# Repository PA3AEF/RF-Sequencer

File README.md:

# **RF‑Sequencer**

The RF‑Sequencer provides deterministic, safe, and hardware‑independent control of RF transmit and receive path transitions.  
It is designed for radio systems that require strict sequencing, amplifier protection, and predictable relay behavior under all conditions.

The firmware architecture emphasizes clarity, safety, and long‑term maintainability.  
Relay hardware, timing rules, and protection logic are abstracted behind stable interfaces, ensuring consistent operation across diverse station configurations.
Earlier work, such as the concepts published by W1GHZ (Paul Wade) helped establish the fundamental principles of safe RF path control.
This RF‑Sequencer continues that lineage with a modern, firmware‑driven architecture that emphasizes clarity, determinism, and long‑term maintainability.

## **Key Features**

- Deterministic transmit/receive sequencing  
- Integrated protection engine with SAFE‑mode enforcement  
- High‑speed ADC sampling for forward and reflected power  
- VSWR and fast reflected‑spike protection (REF_FAST)
- Hardware‑independent relay abstraction  
- Support for monostable and latching relays  
- Configurable timing and topology  
- Structured event output for external integration  
- Minimal configuration surface  
- Designed for reliability in demanding RF environments  

## **Why Another Sequencer?**

Existing RF sequencers, including the influential **W1GHZ Mark 5**, proved that microcontroller‑based protection can outperform analog timing chains. But modern stations demand more: deterministic firmware behavior, structured telemetry, remote monitoring, fault latching, and safe operation in unattended or tower‑top installations.

This project was created to provide:

- A **fully deterministic** main‑loop architecture  
- **Sub‑millisecond protection paths** (REF_FAST)  
- A **machine‑readable event stream** for dashboards and automation  
- A **human‑readable logging channel** for operators  
- A **calibration system** that adapts to any coupler  
- A **robust SAFE‑mode model** suitable for remote sites  

In short: it’s a **next‑generation MCU sequencer**, built on the ideas that came before but engineered for today’s RF environments.

## **Documentation**

The documentation is organized into several focused areas:

### **Overview**
High‑level conceptual introduction to the system.  
- `docs/overview/overview.md`

### **Architecture**
Detailed subsystem specifications and internal design.  
- `docs/architecture/firmware-architecture.md`  
- `docs/architecture/relay-architecture.md`

### **Integration**
External systems can interact with the sequencer through a structured event stream.  
Events reflect internal state transitions, protection triggers, relay actions, and measurement updates.   
Guidance for consuming sequencer events and coordinating external systems:
- `docs/integration/event-monitoring-example.md`
- `docs/integration/integration-examples.md`
- `docs/integration/integration-guide.md`

### **Quickstart**
Installation‑specific setup and basic configuration.  
- `docs/quickstart/quickstart.md`

### **Reference (optional)**
Command‑line reference, event definitions, and configuration schema.  
- `docs/reference/`

## **Design Philosophy**

The RF‑Sequencer is built around several core principles:

- **Safety first** — protection logic overrides all other behavior  
- **Determinism** — no asynchronous state changes  
- **Hardware abstraction** — relay details are isolated behind stable interfaces  
- **Minimal configuration** — only essential structural parameters are exposed  
- **Predictability** — timing and transitions follow strict rules  

These principles ensure reliable operation in both simple and complex RF installations.

## **Contributing**

Contributions that improve clarity, safety, or maintainability are welcome.  
Please ensure that changes preserve the architectural principles described in the documentation.

# **License**

This project uses a dual‑license model:

- **Firmware:** binary‑only, see `LICENSE_FIRMWARE.md`
- **Hardware:** CERN OHL‑P, see `LICENSE_HARDWARE.md`

A human‑readable summary is provided in:

- `LICENSE_NOTICE.md`

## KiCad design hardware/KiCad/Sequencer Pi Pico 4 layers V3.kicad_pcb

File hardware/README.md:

# Hardware

Everything rekated to Hardware.  PCB's (4 layers!) can be easily ordered from JLCPCB. Submit the production ZIP file located in the PCB section. Files are provided for PCBA (PCB Assembly) but it is expensive for small series. Some experience with SMDsoldering is required.

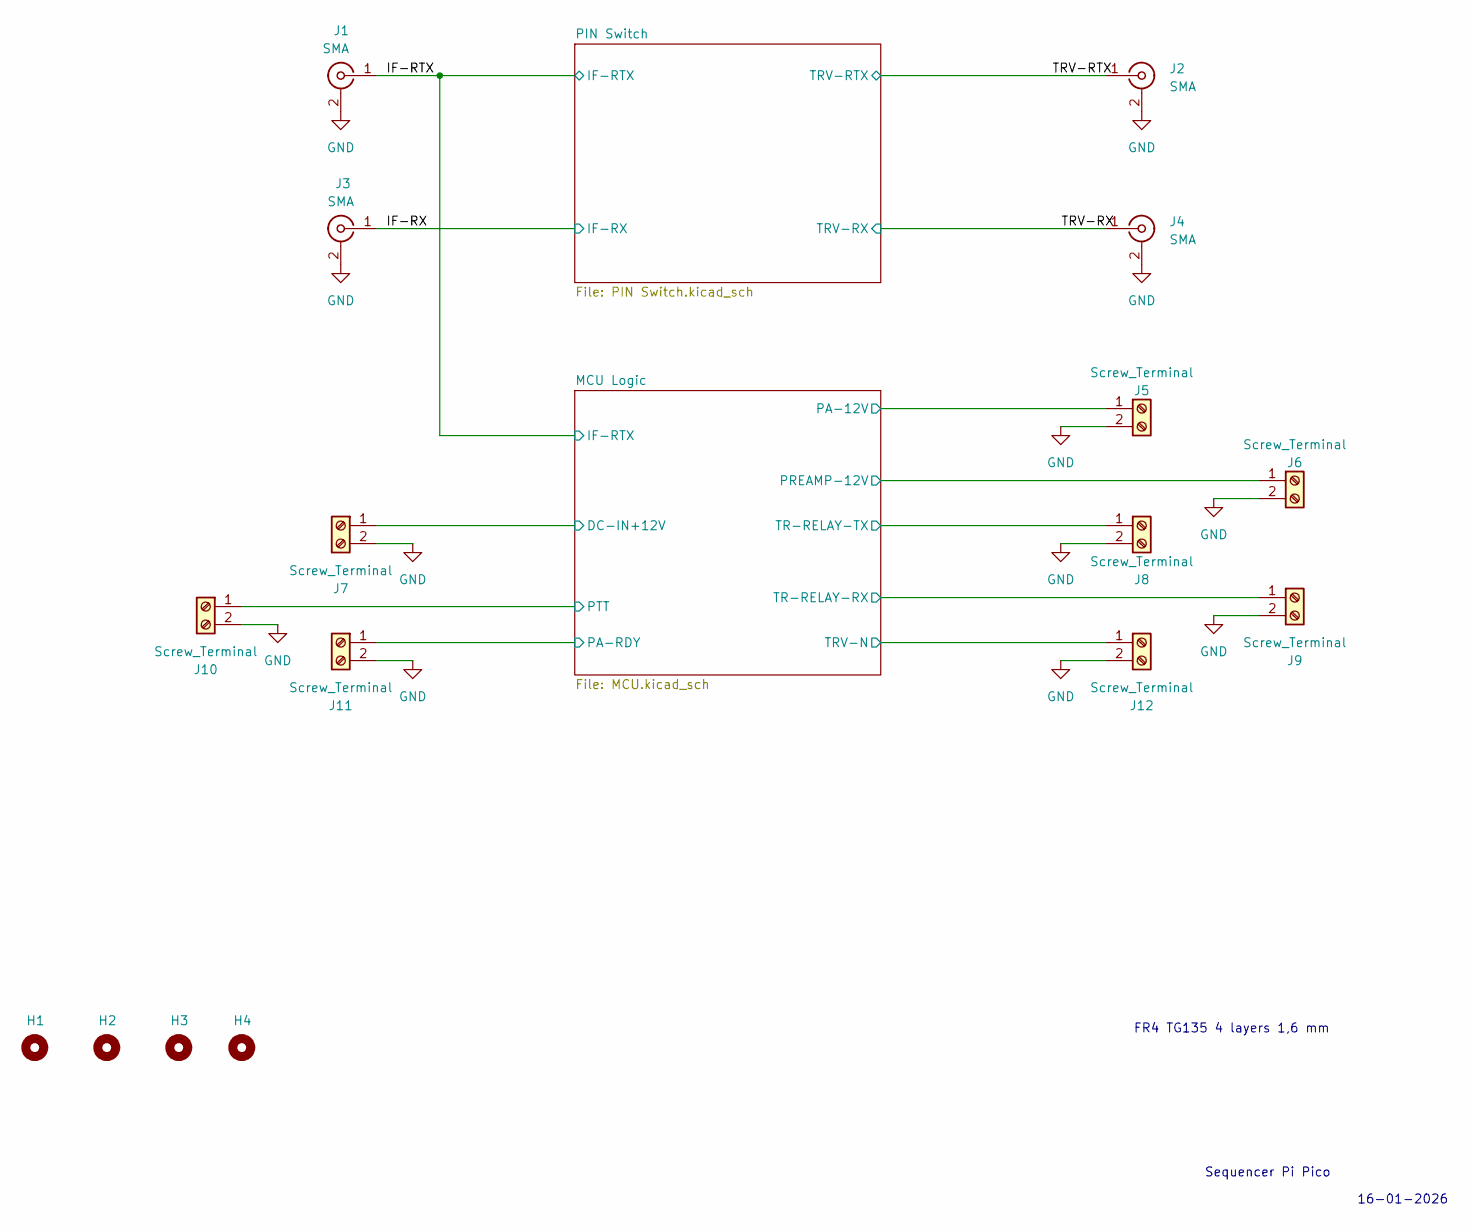
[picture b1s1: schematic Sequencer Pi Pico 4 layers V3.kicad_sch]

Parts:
H1, H2, H3, H4: MountingHole; MountingHole_3.2mm_M3_DIN965_Pad
J1, J2, J3, J4: SMA; SMA_Samtec_SMA-J-P-H-ST-EM1_EdgeMount
J5, J6, J7, J8, J9, J10, J11, J12: Screw_Terminal; Screw terminal 3 pin

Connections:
+12V: J7.1; also elsewhere on the board
/IF-RTX: J1.1 (In); also elsewhere on the board
/IF-RX: J3.1 (In); also elsewhere on the board
/MCU Logic/PA-12V: J5.1; also elsewhere on the board
/MCU Logic/PA-RDY: J11.1; also elsewhere on the board
/MCU Logic/PREAMP-12V: J6.1; also elsewhere on the board
/MCU Logic/PTT: J10.1; also elsewhere on the board
/MCU Logic/TR-RELAY-RX: J9.1; also elsewhere on the board
/MCU Logic/TR-RELAY-TX: J8.1; also elsewhere on the board
/MCU Logic/TRV-N: J12.1; also elsewhere on the board
/TRV-RTX: J2.1 (In); also elsewhere on the board
/TRV-RX: J4.1 (In); also elsewhere on the board
GND: J1.2 (Ext), J2.2 (Ext), J3.2 (Ext), J4.2 (Ext), J5.2, J6.2, J7.2, J8.2, J9.2, J10.2, J11.2, J12.2; also elsewhere on the board

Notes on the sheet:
16-01-2026
FR4 TG135 4 layers 1,6 mm
Sequencer Pi Pico

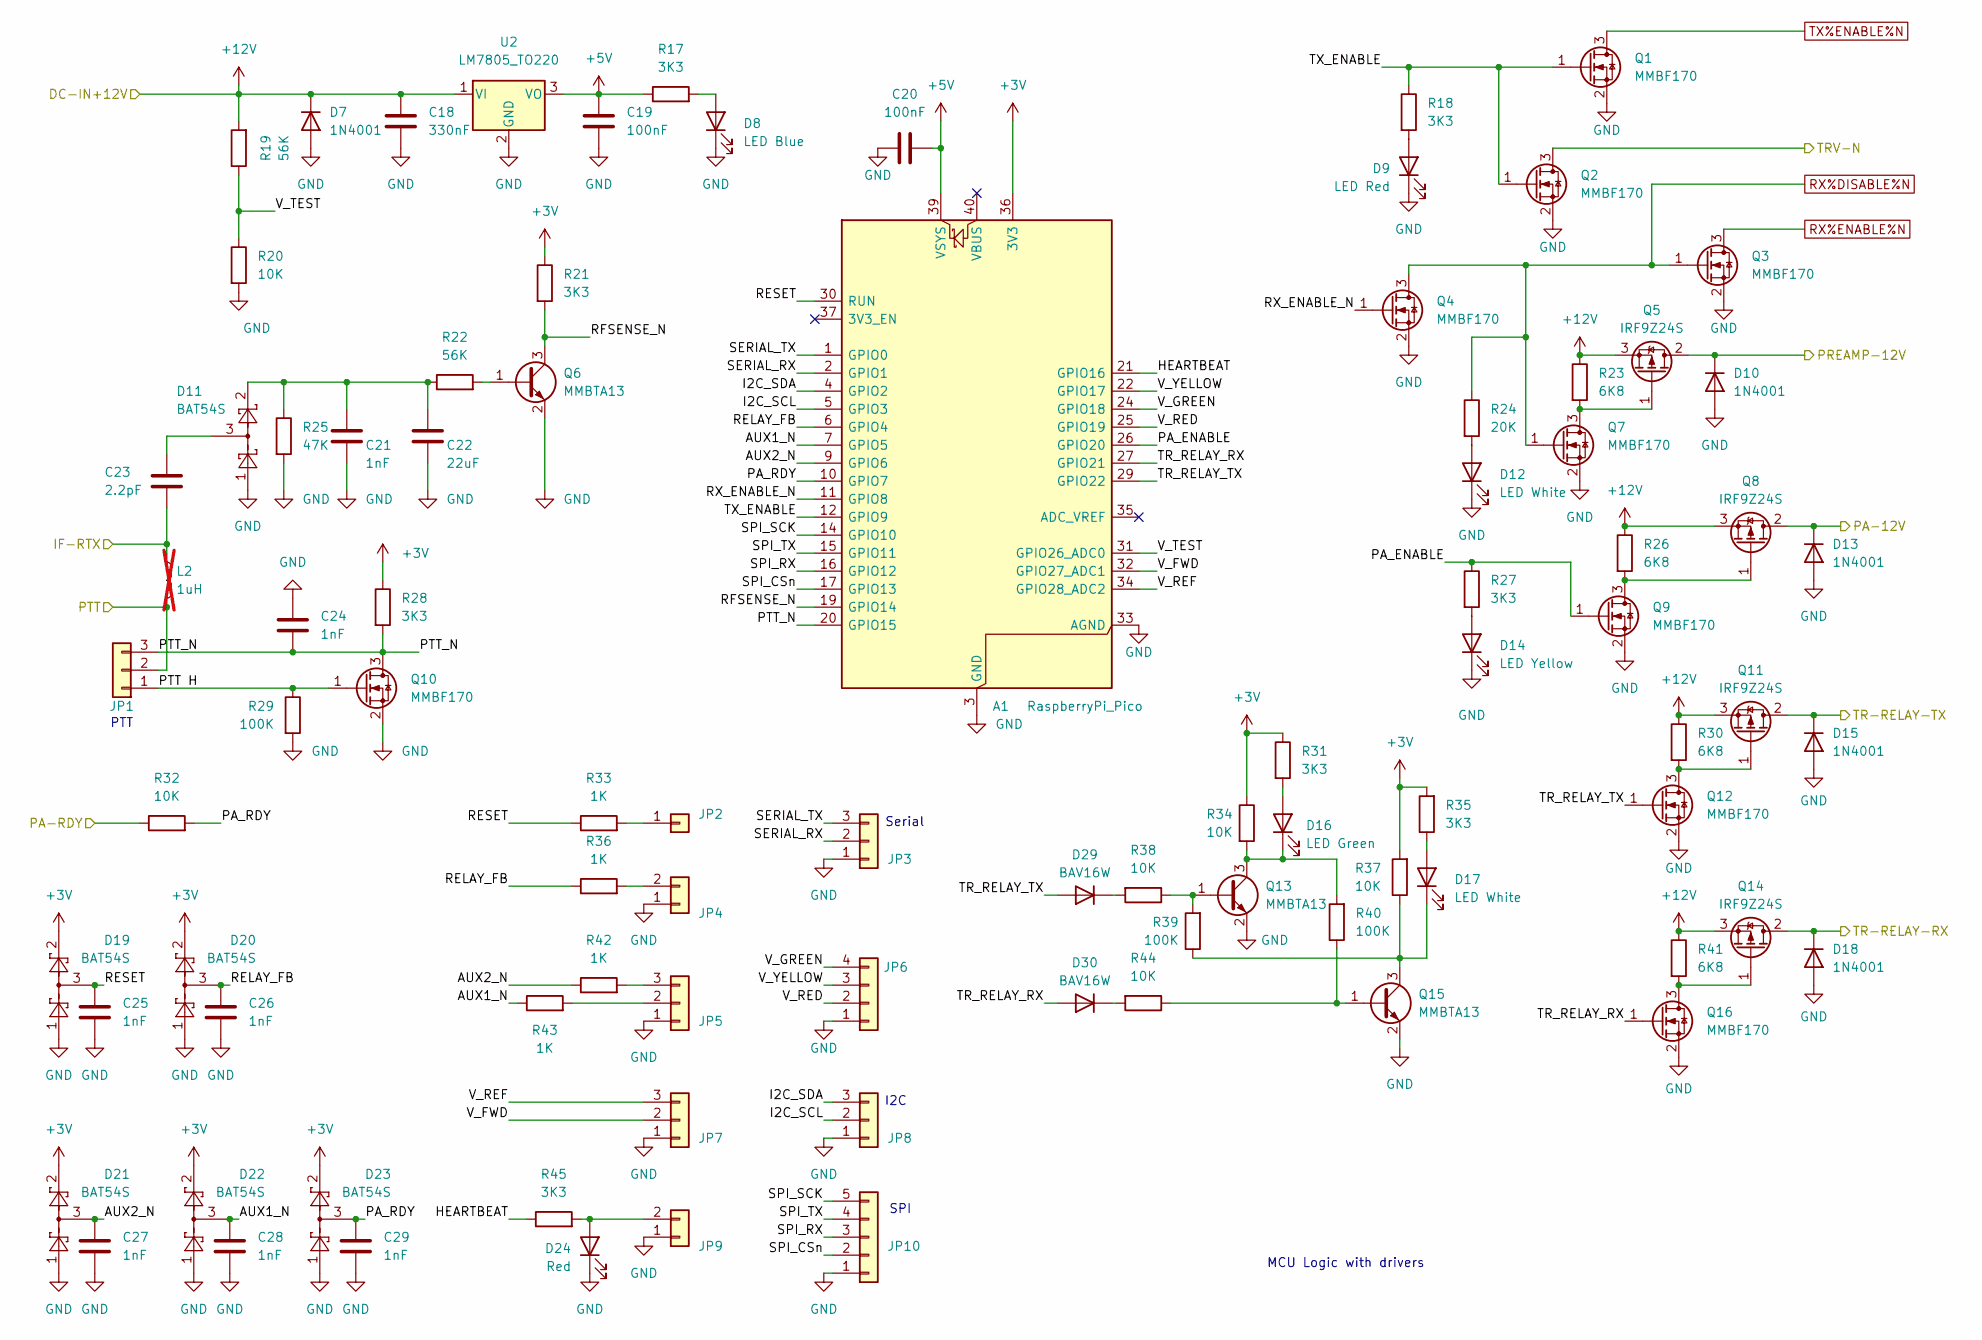
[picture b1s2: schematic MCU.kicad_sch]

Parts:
A1: RaspberryPi_Pico; RaspberryPi_Pico_Common_THT
C18: 330nF; C_0805_2012Metric_Pad1.18x1.45mm_HandSolder
C19, C20: 100nF; C_0805_2012Metric_Pad1.18x1.45mm_HandSolder
C21, C24, C25, C26, C27, C28, C29: 1nF; C_0805_2012Metric_Pad1.18x1.45mm_HandSolder
C22: 22uF; C_0805_2012Metric_Pad1.18x1.45mm_HandSolder
C23: 2.2pF; C_0805_2012Metric_Pad1.18x1.45mm_HandSolder
D7, D10, D13, D15, D18: 1N4001; D_SMA; LCSC C2456
D8: LED Blue; LED_0805_2012Metric_Pad1.15x1.40mm_HandSolder
D9: LED Red; LED_0805_2012Metric_Pad1.15x1.40mm_HandSolder
D11, D19, D20, D21, D22, D23: BAT54S; SOT-23; LCSC C8592
D12, D17: LED White; LED_0805_2012Metric_Pad1.15x1.40mm_HandSolder
D14: LED Yellow; LED_0805_2012Metric_Pad1.15x1.40mm_HandSolder
D16: LED Green; LED_0805_2012Metric_Pad1.15x1.40mm_HandSolder
D24: Red; LED_0805_2012Metric_Pad1.15x1.40mm_HandSolder
D29, D30: BAV16W; D_SOD-323_HandSoldering
JP1, JP3, JP5, JP7, JP8: Conn_01x03; PinHeader_1x03_P2.54mm_Vertical
JP2: Conn_01x01; PinHeader_1x01_P2.54mm_Vertical
JP4, JP9: Conn_01x02; PinHeader_1x02_P2.54mm_Vertical
JP6: Conn_01x04; PinHeader_1x04_P2.54mm_Vertical
JP10: Conn_01x05; PinHeader_1x05_P2.54mm_Vertical
L2: 1uH; L_1008_2520Metric_Pad1.43x2.20mm_HandSolder; not fitted
Q1, Q2, Q3, Q4, Q7, Q9, Q10, Q12, Q16: MMBF170; SOT-23; LCSC C130879
Q5, Q8, Q11, Q14: IRF9Z24S; TO-220-3_Vertical; LCSC C2576
Q6, Q13, Q15: MMBTA13; SOT-23; LCSC C8520
R17, R18, R21, R27, R28, R31, R35, R45: 3K3; R_0805_2012Metric_Pad1.20x1.40mm_HandSolder
R19, R22: 56K; R_0805_2012Metric_Pad1.20x1.40mm_HandSolder
R20, R32, R34, R37, R38, R44: 10K; R_0805_2012Metric_Pad1.20x1.40mm_HandSolder
R23, R26, R30, R41: 6K8; R_0805_2012Metric_Pad1.20x1.40mm_HandSolder
R24: 20K; R_0805_2012Metric_Pad1.20x1.40mm_HandSolder
R25: 47K; R_0805_2012Metric_Pad1.20x1.40mm_HandSolder
R29, R39, R40: 100K; R_0805_2012Metric_Pad1.20x1.40mm_HandSolder
R33, R36, R42, R43: 1K; R_0805_2012Metric_Pad1.20x1.40mm_HandSolder
U2: LM7805_TO220; TO-220-3_Vertical

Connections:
+3V: A1.36 (3V3), D19.2 (K), D20.2 (K), D21.2 (K), D22.2 (K), D23.2 (K), R21.1, R28.1, R31.1, R34.1, R35.2, R37.2
+5V: A1.39 (VSYS), C19.2, C20.1, R17.1, U2.3 (VO); also elsewhere on the board
+12V: C18.2, D7.1 (K), Q5.3 (S), Q8.3 (S), Q11.3 (S), Q14.3 (S), R19.2, R23.1, R26.1, R30.1, R41.1, U2.1 (VI); also elsewhere on the board
/IF-RTX: C23.1, L2.1; also elsewhere on the board
/MCU Logic/AUX1_N: A1.7 (GPIO5), C28.1, D22.3 (COM), R43.1
/MCU Logic/AUX2_N: A1.9 (GPIO6), C27.1, D21.3 (COM), R42.1
/MCU Logic/HEARTBEAT: A1.21 (GPIO16), R45.1
/MCU Logic/I2C_SCL: A1.5 (GPIO3), JP8.2
/MCU Logic/I2C_SDA: A1.4 (GPIO2), JP8.3
/MCU Logic/PA-12V: D13.1 (K), Q8.2 (D); also elsewhere on the board
/MCU Logic/PA-RDY: R32.1; also elsewhere on the board
/MCU Logic/PA_ENABLE: A1.26 (GPIO20), Q9.1 (G), R27.1
/MCU Logic/PA_RDY: A1.10 (GPIO7), C29.1, D23.3 (COM), R32.2
/MCU Logic/PREAMP-12V: D10.1 (K), Q5.2 (D); also elsewhere on the board
/MCU Logic/PTT: JP1.2, L2.2; also elsewhere on the board
/MCU Logic/PTT H: JP1.1, Q10.1 (G), R29.1
/MCU Logic/PTT_N: A1.20 (GPIO15), C24.2, JP1.3, Q10.3 (D), R28.2
/MCU Logic/RELAY_FB: A1.6 (GPIO4), C26.1, D20.3 (COM), R36.1
/MCU Logic/RESET: A1.30 (RUN), C25.1, D19.3 (COM), R33.1
/MCU Logic/RFSENSE_N: A1.19 (GPIO14), Q6.3 (C), R21.2
/MCU Logic/RX_ENABLE_N: A1.11 (GPIO8), Q4.1 (G)
/MCU Logic/SERIAL_RX: A1.2 (GPIO1), JP3.2
/MCU Logic/SERIAL_TX: A1.1 (GPIO0), JP3.3
/MCU Logic/SPI_CSn: A1.17 (GPIO13), JP10.2
/MCU Logic/SPI_RX: A1.16 (GPIO12), JP10.3
/MCU Logic/SPI_SCK: A1.14 (GPIO10), JP10.5
/MCU Logic/SPI_TX: A1.15 (GPIO11), JP10.4
/MCU Logic/TR-RELAY-RX: D18.1 (K), Q14.2 (D); also elsewhere on the board
/MCU Logic/TR-RELAY-TX: D15.1 (K), Q11.2 (D); also elsewhere on the board
/MCU Logic/TRV-N: Q2.3 (D); also elsewhere on the board
/MCU Logic/TR_RELAY_RX: A1.27 (GPIO21), D30.2 (A), Q16.1 (G)
/MCU Logic/TR_RELAY_TX: A1.29 (GPIO22), D29.2 (A), Q12.1 (G)
/MCU Logic/TX_ENABLE: A1.12 (GPIO9), Q1.1 (G), Q2.1 (G), R18.1
/MCU Logic/V_FWD: A1.32 (GPIO27_ADC1), JP7.2
/MCU Logic/V_GREEN: A1.24 (GPIO18), JP6.4
/MCU Logic/V_RED: A1.25 (GPIO19), JP6.2
/MCU Logic/V_REF: A1.34 (GPIO28_ADC2), JP7.3
/MCU Logic/V_TEST: A1.31 (GPIO26_ADC0), R19.1, R20.1
/MCU Logic/V_YELLOW: A1.22 (GPIO17), JP6.3
GND: A1.3 (GND), A1.8 (GND), A1.13 (GND), A1.18 (GND), A1.23 (GND), A1.28 (GND), A1.33 (AGND), A1.38 (GND), C18.1, C19.1, C20.2, C21.1, C22.1, C24.1, C25.2, C26.2, C27.2, C28.2, C29.2, D7.2 (A), D8.1 (K), D9.1 (K), D10.2 (A), D11.1 (A), D12.1 (K), D13.2 (A), D14.1 (K), D15.2 (A), D18.2 (A), D19.1 (A), D20.1 (A), D21.1 (A), D22.1 (A), D23.1 (A), D24.1 (K), JP3.1, JP4.1, JP5.1, JP6.1, JP7.1, JP8.1, JP9.1, JP10.1, Q1.2 (S), Q2.2 (S), Q3.2 (S), Q4.2 (S), Q6.2 (E), Q7.2 (S), Q9.2 (S), Q10.2 (S), Q12.2 (S), Q13.2 (E), Q15.2 (E), Q16.2 (S), R20.2, R25.2, R29.2, U2.2 (GND); also elsewhere on the board
unnamed: D8.2 (A), R17.2
unnamed: D9.2 (A), R18.2
unnamed: C23.2, D11.3 (COM)
unnamed: C21.2, C22.2, D11.2 (K), R22.1, R25.1
unnamed: D12.2 (A), R24.2
unnamed: D14.2 (A), R27.2
unnamed: D16.2 (A), R31.2
unnamed: D16.1 (K), Q13.3 (C), R34.2, R40.2
unnamed: D17.2 (A), R35.1
unnamed: D17.1 (K), Q15.3 (C), R37.1, R39.1
unnamed: D24.2 (A), JP9.2, R45.2
unnamed: D29.1 (K), R38.2
unnamed: D30.1 (K), R44.2
unnamed: JP2.1, R33.2
unnamed: JP4.2, R36.2
unnamed: JP5.2, R43.2
unnamed: JP5.3, R42.2
unnamed: Q5.1 (G), Q7.3 (D), R23.2
unnamed: Q6.1 (B), R22.2
unnamed: Q8.1 (G), Q9.3 (D), R26.2
unnamed: Q11.1 (G), Q12.3 (D), R30.2
unnamed: Q13.1 (B), R38.1, R39.2
unnamed: Q14.1 (G), Q16.3 (D), R41.2
unnamed: Q15.1 (B), R40.1, R44.1
RX%DISABLE%N: Q3.1 (G), Q4.3 (D), Q7.1 (G), R24.1; also elsewhere on the board
RX%ENABLE%N: Q3.3 (D); also elsewhere on the board
TX%ENABLE%N: Q1.3 (D); also elsewhere on the board

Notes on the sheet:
Serial
I2C
SPI
MCU Logic with drivers
PTT

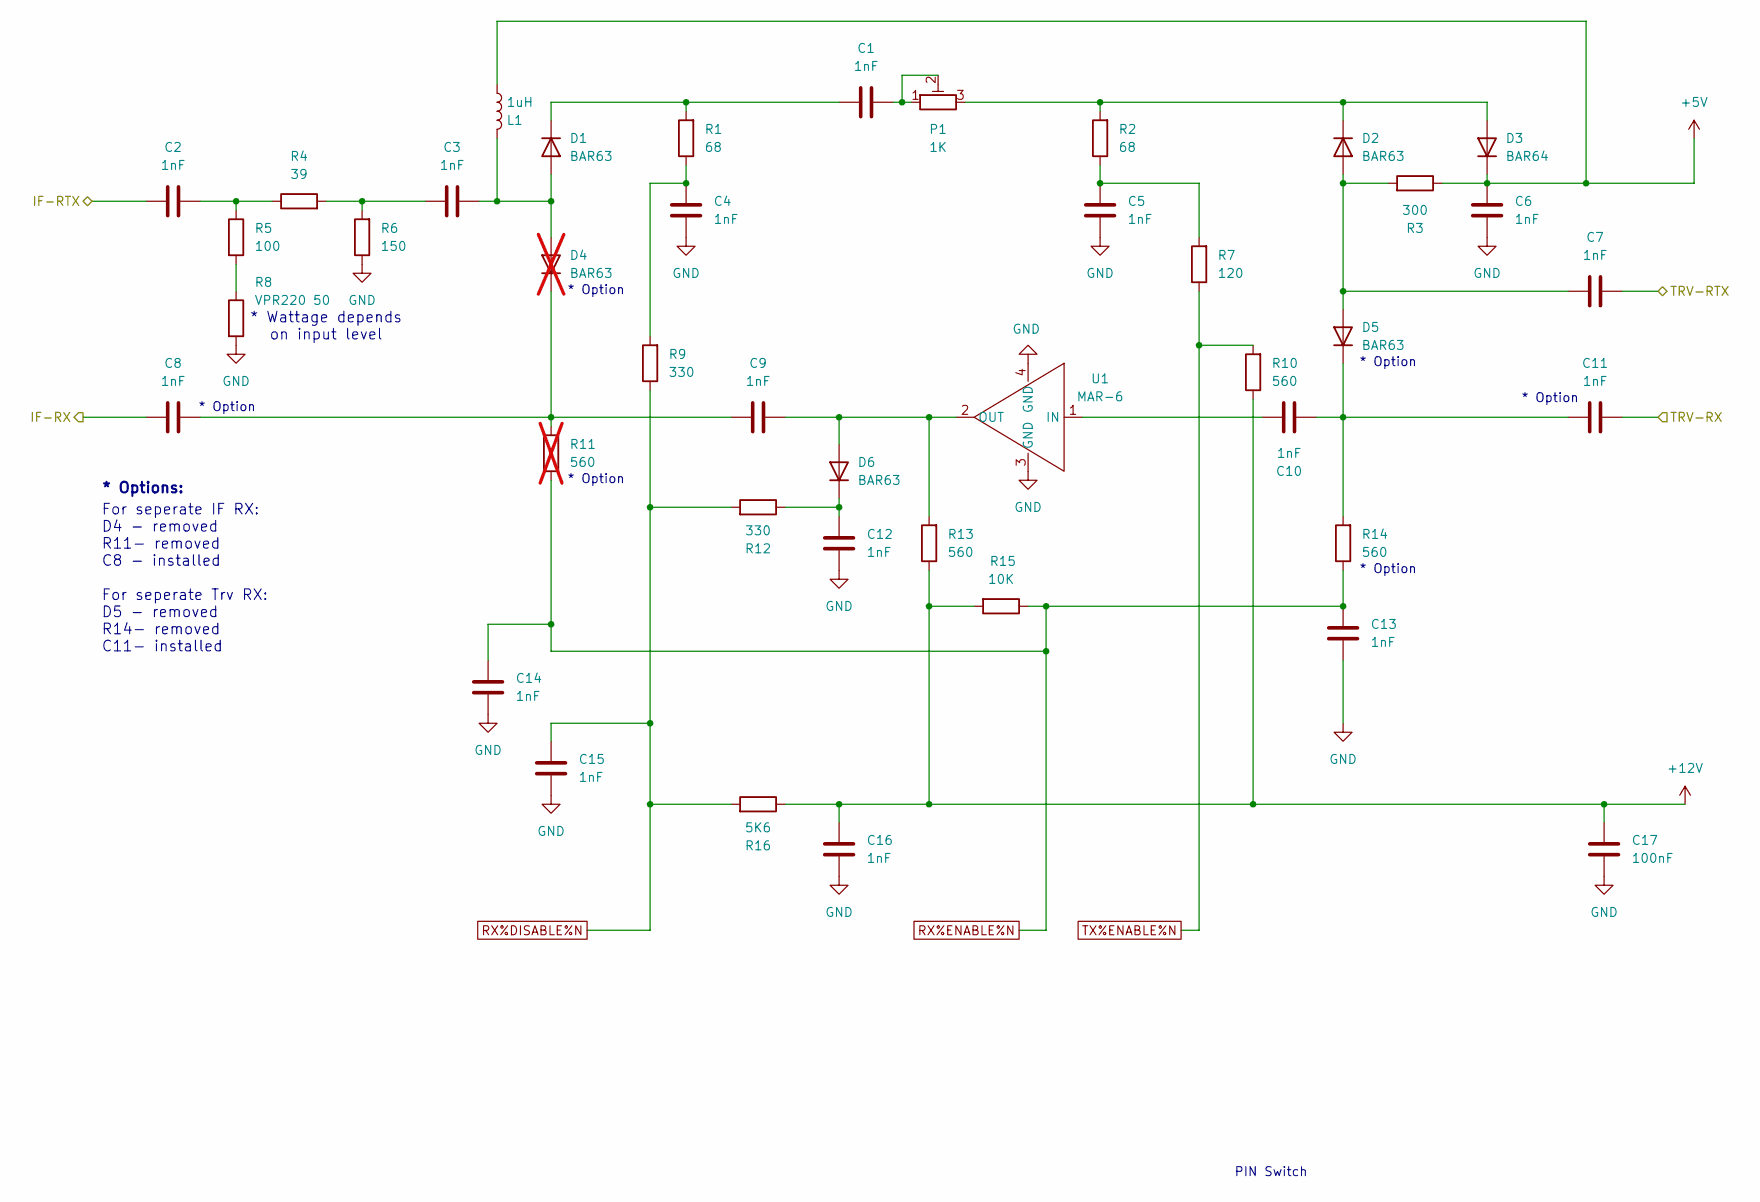
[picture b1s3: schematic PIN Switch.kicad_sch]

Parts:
C1, C2, C3, C4, C5, C6, C7, C8, C9, C10, C11, C12, C13, C14, C15, C16: 1nF; C_0805_2012Metric_Pad1.18x1.45mm_HandSolder
C17: 100nF; C_0805_2012Metric_Pad1.18x1.45mm_HandSolder
D1, D2, D5, D6: BAR63; D_SOD-323_HandSoldering
D3: BAR64; D_SOD-323_HandSoldering
D4: BAR63; D_SOD-323_HandSoldering; not fitted
L1: 1uH; L_1008_2520Metric_Pad1.43x2.20mm_HandSolder
P1: 1K; Potentiometer_Bourns_3314G_Vertical; LCSC C780221
R1, R2: 68; R_0805_2012Metric_Pad1.20x1.40mm_HandSolder
R3: 300; R_0805_2012Metric_Pad1.20x1.40mm_HandSolder
R4: 39; R_0805_2012Metric_Pad1.20x1.40mm_HandSolder
R5: 100; R_0805_2012Metric_Pad1.20x1.40mm_HandSolder
R6: 150; R_0805_2012Metric_Pad1.20x1.40mm_HandSolder
R7: 120; R_0805_2012Metric_Pad1.20x1.40mm_HandSolder
R8: VPR220 50; TO-220-2_Vertical Resistor
R9, R12: 330; R_0805_2012Metric_Pad1.20x1.40mm_HandSolder
R10, R13, R14: 560; R_0805_2012Metric_Pad1.20x1.40mm_HandSolder
R11: 560; R_0805_2012Metric_Pad1.20x1.40mm_HandSolder; not fitted
R15: 10K; R_0805_2012Metric_Pad1.20x1.40mm_HandSolder
R16: 5K6; R_0805_2012Metric_Pad1.20x1.40mm_HandSolder
U1: MAR-6; MSA_1

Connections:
+5V: C6.2, D3.1 (K), L1.2, R3.1; also elsewhere on the board
+12V: C16.2, C17.2, R10.1, R13.1, R15.2, R16.1; also elsewhere on the board
/IF-RTX: C2.1; also elsewhere on the board
/IF-RX: C8.1; also elsewhere on the board
/TRV-RTX: C7.2; also elsewhere on the board
/TRV-RX: C11.2; also elsewhere on the board
GND: C4.1, C5.1, C6.1, C12.1, C13.1, C14.1, C15.1, C16.1, C17.1, R6.1, R8.2, U1.3 (GND), U1.4 (GND); also elsewhere on the board
unnamed: C1.2, P1.1, P1.2
unnamed: C2.2, R4.1, R5.1
unnamed: C3.1, R4.2, R6.2
unnamed: C4.2, R1.1, R9.2
unnamed: C5.2, R2.1, R7.2
unnamed: C3.2, D1.2 (A), D4.2 (A), L1.1
unnamed: C1.1, D1.1 (K), R1.2
unnamed: C7.1, D2.2 (A), D5.2 (A), R3.2
unnamed: D2.1 (K), D3.2 (A), P1.3, R2.2
unnamed: C8.2, C9.1, D4.1 (K), R11.2
unnamed: C10.2, C11.1, D5.1 (K), R14.2
unnamed: C9.2, D6.2 (A), R13.2, U1.2 (OUT)
unnamed: C12.2, D6.1 (K), R12.1
unnamed: R5.2, R8.1
unnamed: C10.1, U1.1 (IN)
RX%DISABLE%N: C15.2, R9.1, R12.2, R16.2; also elsewhere on the board
RX%ENABLE%N: C13.2, C14.2, R11.1, R14.1, R15.1; also elsewhere on the board
TX%ENABLE%N: R7.1, R10.2; also elsewhere on the board

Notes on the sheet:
* Option
* Wattage depends on input level
For seperate IF RX: D4 - removed R11- removed C8 - installed For seperate Trv RX: D5 - removed R14- removed C11- installed
PIN Switch
* Options:

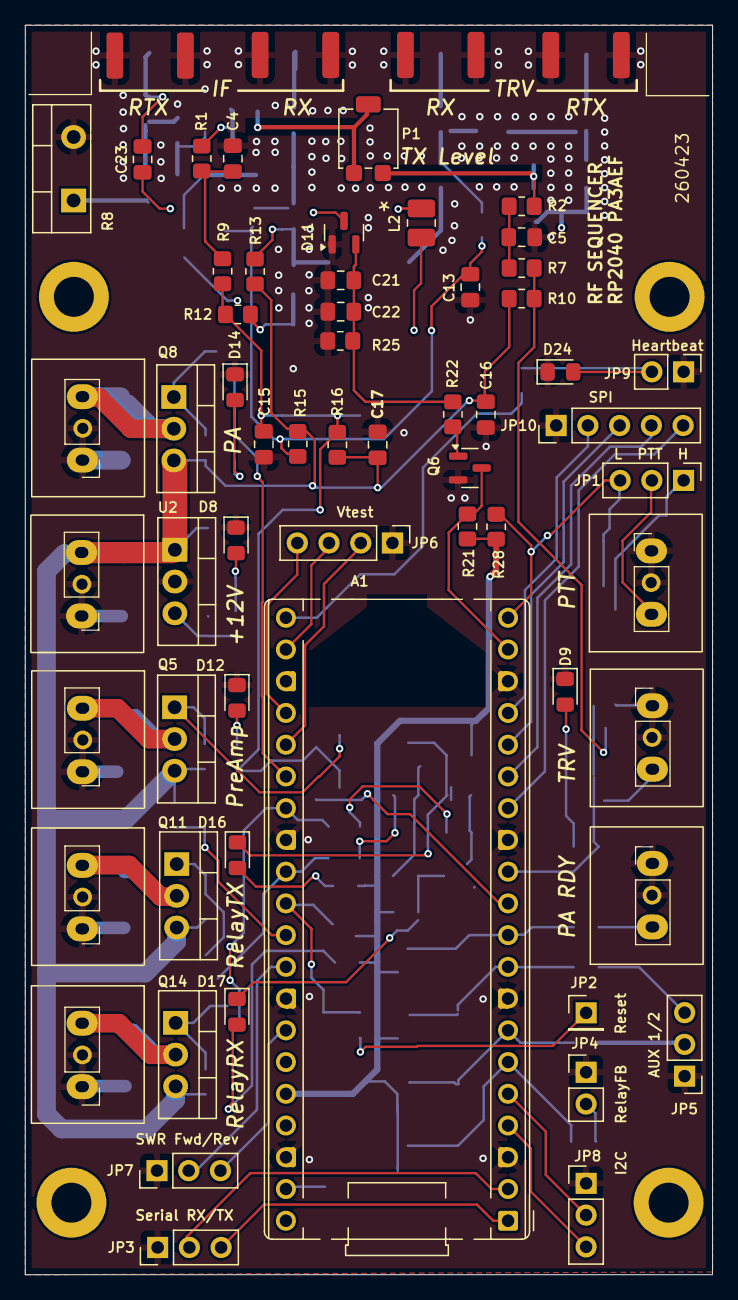
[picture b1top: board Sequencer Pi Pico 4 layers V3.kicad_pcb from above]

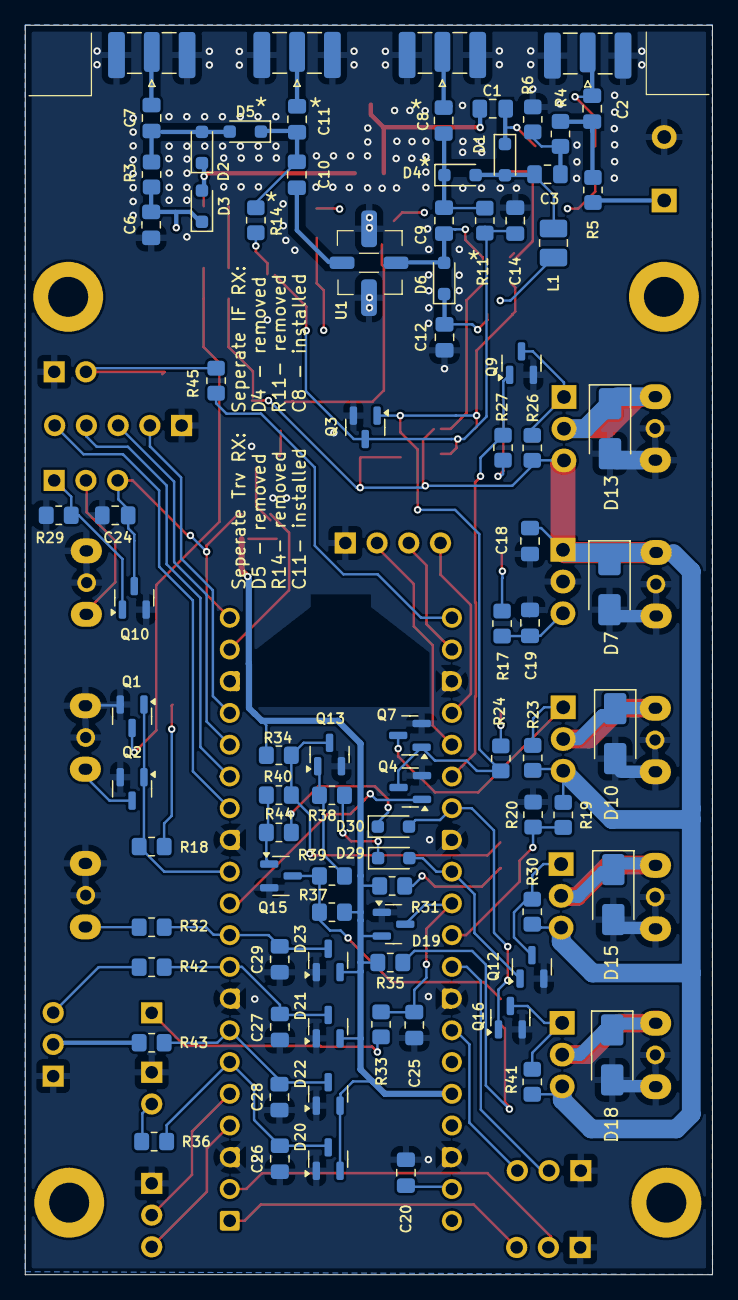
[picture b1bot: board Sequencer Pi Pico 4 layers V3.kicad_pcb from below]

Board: 4 copper layers, 55.0 x 100.0 mm, 148 parts (86 on the bottom side), 85 nets.

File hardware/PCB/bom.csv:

Designator,Footprint,Quantity,Value,LCSC Part #
A1,RaspberryPi_Pico_Common_THT,1,RaspberryPi_Pico,
"C1, C10, C11, C12, C13, C14, C15, C16, C2, C21, C24, C25, C26, C27, C28, C29, C3, C4, C5, C6, C7, C8, C9",0805,23,1nF,
"C17, C19, C20",0805,3,100nF,
C18,0805,1,330nF,
C22,0805,1,22uF,
C23,0805,1,2.2pF,
"D1, D2, D5, D6",D_SOD-323_HandSoldering,4,BAR63,
"D10, D13, D15, D18, D7",D_SMA,5,1N4001,C2456
"D11, D19, D20, D21, D22, D23",SOT-23,6,BAT54S,C8592
"D12, D17",0805,2,LED White,
D14,0805,1,LED Yellow,
D16,0805,1,LED Green,
D24,0805,1,Red,
"D29, D30",D_SOD-323_HandSoldering,2,BAV16W,
D3,D_SOD-323_HandSoldering,1,BAR64,
D8,0805,1,LED Blue,
D9,0805,1,LED Red,
"J1, J2, J3, J4",SMA_Samtec_SMA-J-P-H-ST-EM1_EdgeMount,4,SMA,
"J10, J11, J12, J5, J6, J7, J8, J9",Screw terminal 3 pin,8,Screw_Terminal,
"JP1, JP3, JP5, JP7, JP8",PinHeader_1x03_P2.54mm_Vertical,5,Conn_01x03,
JP10,PinHeader_1x05_P2.54mm_Vertical,1,Conn_01x05,
JP2,PinHeader_1x01_P2.54mm_Vertical,1,Conn_01x01,
"JP4, JP9",PinHeader_1x02_P2.54mm_Vertical,2,Conn_01x02,
JP6,PinHeader_1x04_P2.54mm_Vertical,1,Conn_01x04,
L1,1008,1,1uH,
P1,Potentiometer_Bourns_3314G_Vertical,1,1K,C780221
"Q1, Q10, Q12, Q16, Q2, Q3, Q4, Q7, Q9",SOT-23,9,MMBF170,C130879
"Q11, Q14, Q5, Q8",TO-220-3_Vertical,4,IRF9Z24S,C2576
"Q13, Q15, Q6",SOT-23,3,MMBTA13,C8520
"R1, R2",0805,2,68,
"R10, R13, R14",0805,3,560,
"R12, R9",0805,2,330,
"R15, R20, R32, R34, R37, R38, R44",0805,7,10K,
R16,0805,1,5K6,
"R17, R18, R21, R27, R28, R31, R35, R45",0805,8,3K3,
"R19, R22",0805,2,56K,
"R23, R26, R30, R41",0805,4,6K8,
R24,0805,1,20K,
R25,0805,1,47K,
"R29, R39, R40",0805,3,100K,
R3,0805,1,300,
"R33, R36, R42, R43",0805,4,1K,
R4,0805,1,39,
R5,0805,1,100,
R6,0805,1,150,
R7,0805,1,120,
R8,TO-220-2_Vertical Resistor,1,VPR220 50,
U1,MSA_1,1,MAR-6,
U2,TO-220-3_Vertical,1,LM7805_TO220,

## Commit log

2026-02-13 Initial commit with latest files
2026-02-13 Remove optional latest
2026-02-13 Update versioning
2026-04-08 News on frimware
2026-04-08 Added changelog and relay architecture
2026-04-08 typos
2026-04-08 typo
2026-04-11 Added new relay topology (latching relays etc.)
2026-04-11 Add files via upload
    Production files
2026-04-11 New files for PCB
2026-04-11 deleted: hardware/README modified: hardware/README.md
2026-04-12 Image in README
2026-04-12 Image in REDAME Changes to be committed: modified: README.md deleted: img/RF_Sequencer_T1.png new file: img/RF_Sequencer_T1_0.5.png
2026-04-12 modified: docs/architecture/integration-examples.md modified: docs/firmware/README.md modified: docs/firmware/adc.md modified: docs/firmware/statemachine.md modified: hardware/README.md
2026-04-12 Updated CLI commands
2026-04-12 Update reference to CLI commands
2026-04-12 Firmware V1.2 for V3 board
2026-04-14 Enhanced doc structure
2026-04-23 Fixed circuit for latched relays
2026-04-25 New firmware matching latched relays
2026-06-10 Refactor documentation structure and add missing files for RF-Sequencer
2026-06-11 Update navigation URLs for improved documentation structure
2026-06-12 Fix firmware link in documentation to point to README.md
2026-06-28 Remove outdated documentation files and add new architecture overview
2026-06-28 Remove navigation configuration file from documentation
